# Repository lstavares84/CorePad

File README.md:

# CorePad — Beta Carbon

Macropad USB-C com **9 teclas em 3 × 3**, biometria, controle de áudio e gravação de reuniões. A linha escolhida para desenvolvimento é a **Beta**, com acabamento em aparência de fibra de carbono e faixa RGB configurável exclusivamente na base.

O [Caderno de Engenharia Rev. A em PDF](docs/engineering/Rev_A/CorePad_Caderno_de_Engenharia_Rev_A.pdf) consolida requisitos, eletrônica, mecânica, firmware, software, qualidade, riscos e pendências em 65 lâminas A3. Consulte o [índice e instruções de reprodução](docs/engineering/Rev_A/README.md). O caderno é uma linha de base de engenharia; fabricação permanece bloqueada pelos itens “A DEFINIR”.

## RGB — cinco cores

Galeria da [Beta 1.0.1](beta_blender/Beta_v1.0.1.blend), renderizada em 2000 × 1700 pixels com a mesma câmera e iluminação. A revisão refina a trama twill 2 × 2 de carbono, filamentos, resina, microtexturas e reflexos, e acrescenta um anteparo interno à faixa RGB.

| Laranja | Amarelo |
|---|---|
|  |  |
| Cor de referência sRGB `#FF6A00`. | Cor de referência sRGB `#FFD500`. |

| Verde | Vermelho |
|---|---|
|  |  |
| Cor de referência sRGB `#00FF00`. | Cor de referência sRGB `#FF1200`. |

**Azul — referência sRGB `#0066FF`**

## Produto: vistas técnicas

As vistas de topo, lateral e traseira preservam a documentação geométrica da [Beta 1.0.0](beta_blender/Beta_v1.0.0.blend); o detalhe dos controles usa os materiais refinados da [Beta 1.0.1](beta_blender/Beta_v1.0.1.blend). Elas mostram a organização visual escolhida; o empilhamento interno ainda está em desenvolvimento.

| Vista superior | Controles e biometria |
|---|---|
|  |  |
| Nove teclas sem inscrições, seletor, três indicadores e botão de gravação. | Fader vertical e mudo à direita, com sensor biométrico acessível. |

| Lateral esquerda | Traseira |
|---|---|
|  |  |
| P2 e microSD na lateral esquerda. | USB-C exclusivamente na borda traseira. |

**Detalhe da base — Beta 1.0.1**

Luz difusa junto à mesa, com anteparo interno e sem linha verde superior.

## PCB: estado atual dos arquivos KiCad

**Revisão ativa 0.3.0 — placas e encaixe:** a [PCB UI de duas camadas](development/hardware/v0.3.0/CorePad_UI_v0.3.0.kicad_pcb) contém nove footprints piloto Kailh Choc V2, FFC de 24 vias e **seis de nove sinais de teclas roteados**. A [PCB principal de quatro camadas](development/hardware/v0.3.0/CorePad_Main_v0.3.0.kicad_pcb) posiciona MCU, codec, amplificador, USB-C, microSD, P2 e FFC com footprints candidatos; não possui circuito completo nem trilhas funcionais. Consulte o [guia eletrônico](development/hardware/v0.3.0/README.md), a [pinagem proposta](development/hardware/v0.3.0/interconnect_24.json), a [BOM atualizada dos componentes posicionados](development/hardware/v0.3.0/BOM_DELTA.md) e os relatórios DRC: [UI](development/hardware/v0.3.0/ui_drc.txt) e [principal](development/hardware/v0.3.0/main_drc.txt).

| Trilhas piloto da UI | Componentes candidatos na principal |
|---|---|
|  |  |
| Três sinais de tecla e terra ainda abertos; DRC sem violações geométricas. | Posicionamento apenas; DRC com 8 violações, sem esquema completo. |

O [conjunto STEP integrado 0.2.0](development/integration/v0.2.0/CorePad_Beta_PCB_match_v0.2.0.step) substitui as placas nuas anteriores pelas exportações KiCad 0.3.0 e adiciona envelopes dos componentes e FFC. O [relatório de encaixe](development/integration/v0.2.0/README.md) identifica **choques do USB-C e microSD com a base**, desvio vertical **2,41 mm** entre P2 e abertura, ausência de suportes das placas e dobra do FFC ainda não comprovada. Esses achados impedem liberação para fabricação.

### Estudos anteriores

Os renders abaixo mostram o estudo 0.2.0 de bancada e posicionamento anterior. Não representam as placas ativas 0.3.0.

| Interface de bancada | Placa principal em estudo |
|---|---|
|  |  |
| 15 footprints de conectores, 44 pinos conferidos com o esquema e redes atribuídas. ERC sem erros/avisos; 29 conexões ainda sem trilhas. | Contorno e footprint do STM32U5A5. Áudio, alimentação, segurança, esquema completo e roteamento ainda pendentes. |

A interface usa chicotes para os controles externos e serve à bancada; a placa superior definitiva ainda precisa ser projetada. **As placas atuais não estão liberadas para fabricação.**

O [arquivo KiCad de posicionamento da PCB UI](development/hardware/ui_mechanical/v0.1.0/CorePad_UI_Posicionamento_v0.1.0.kicad_pcb) registra contorno e centros de teclas/controles na mesma referência do 3D; não tem pads, trilhas ou esquema.

**PCB UI mecânica:** nove centros SW1–SW9 e posições de controles; os retângulos mostram janelas da tampa, não footprints de solda.

- [Interface: esquema](development/hardware/v0.2.0/CorePad_Interface_Bancada_v0.2.0.kicad_sch) e [PCB](development/hardware/v0.2.0/CorePad_Interface_Bancada_v0.2.0.kicad_pcb).
- [Principal: PCB em estudo](development/hardware/v0.2.0/CorePad_Principal_v0.2.0.kicad_pcb).
- [BOM por bloco](development/hardware/v0.2.0/BOM.md), [arquitetura de referência](development/hardware/v0.2.0/ARCHITECTURE_REFERENCE.md) e [relatórios ERC/DRC](development/hardware/v0.2.0/reports/).

## Peças plásticas: vistas de engenharia

Renders derivados da [montagem mecânica editável](development/mechanical/v0.1.0/Beta_Pecas_v0.1.0.blend), revisão 0.1.0. As peças são mostradas sem revestimento decorativo para facilitar a leitura dos recortes e volumes.

**Vista explodida:** base isolante, difusor perimetral destacado em verde, tampa com recortes e dois botões. As separações verticais servem à visualização da montagem.

| Interior da base | Tampa vista de cima |
|---|---|
|  |  |
| Canal do difusor, pontes estruturais e aberturas de conectores/microfones. | Recortes das nove teclas, biometria, fader, chave, seletor, LEDs e gravação. |

O estudo mecânico usa **104 × 84 × 28,4 mm**, excluindo comandos. A espessura é exploratória e difere do modelo visual Beta. Cada STL contém um sólido fechado; fixações, suportes de PCB, retenções e tolerâncias dos componentes ainda precisam ser fechados.

## Montagem 3D integrada e desenhos — estudo anterior 0.1.0

O [conjunto STEP 0.1.0](development/integration/v0.1.0/CorePad_Beta_integrado_v0.1.0.step) documenta a geometria original da base, tampa, difusor, bateria e cabos. Usa a [PCB UI mecânica anterior](development/hardware/ui_mechanical/v0.1.0/CorePad_UI_Posicionamento_v0.1.0.kicad_pcb), sem pads/trilhas. A [fonte paramétrica](development/integration/v0.1.0/build_assembly.py), [peças STEP/STL](development/integration/v0.1.0/parts/), [manifesto](development/integration/v0.1.0/assembly_manifest.json) e [relatório anterior](development/integration/v0.1.0/fit_report.json) permanecem como histórico de engenharia. Para conferir a eletrônica atual com a caixa, use a **revisão 0.2.0** ligada acima.

**Conjunto montado:** caixa, placas, bateria, controles e cabos na posição nominal. A vista não prova encaixe de componentes de fornecedor.

As vistas de engenharia usam cinza neutro para leitura das peças; o acabamento escolhido continua sendo o carbono da galeria Beta 1.0.1 acima.

| Montagem explodida | Corpo aberto em posição montada |
|---|---|
|  |  |
| Vista para ler o empilhamento de tampa, PCB UI, PCB principal, bateria e base. | Base transparente de inspeção; conectores e cabos estão em posição proposta. |

**Passagem proposta:** a vista isola o FFC de 16 sinais e os dois fios da bateria; PCB UI, tampa e comandos foram ocultados apenas para inspeção. Conectores, terminação, comprimento e raio de dobra ainda não foram escolhidos.

| Planta cotada preliminar | Seção do empilhamento preliminar |
|---|---|
|  |  |
| Envelope 104 × 84 mm e localização de controles. | Alturas das placas, bateria, tampa e folgas nominais. |

Consulte a [BOM mecânica e de cabos](development/integration/v0.1.0/BOM_MECANICA_CABOS.md) e o [índice de liberação de manufatura](development/integration/v0.1.0/LIBERACAO_MANUFATURA.md). Os desenhos são estudo dimensional; **não são desenhos liberados para fabricar**.

[Base STL](development/mechanical/v0.1.0/Base_plastica.stl) · [Tampa STL](development/mechanical/v0.1.0/Tampa_carbono.stl) · [Difusor STL](development/mechanical/v0.1.0/Difusor_RGB.stl) · [Botão de camada STL](development/mechanical/v0.1.0/Botao_camada.stl) · [Botão de gravação STL](development/mechanical/v0.1.0/Botao_gravacao.stl)

## Software e verificação

O [firmware C11](development/firmware/) contém o núcleo de estados de camadas, cartão, RGB e bateria baixa, testado em host e compilado para Cortex-M33. O [configurador desktop](development/software/configurator.py) edita as 18 macros comuns e RGB, salva JSON e aplica a configuração a um simulador. USB físico, drivers de áudio/cartão, biometria segura e FIDO2 continuam em desenvolvimento.

O [enquadramento de configuração pública](development/software/wire_protocol.py) já valida versão, tamanho, ID de mensagem e CRC32 antes de entregar comandos ao simulador. Ainda não é comunicação USB de produto.

```sh
make -C development/firmware test arm
python3 -m unittest discover -s development/tests -v
python3 development/software/configurator.py
```

Consulte [resultados de validação](development/VALIDATION.md), [estado atual](docs/STATUS.md) e [roteiro](docs/ROADMAP.md). A autonomia de 30 horas permanece como meta de ensaio.

## Continuar o desenvolvimento

Comece por [CLAUDE.md](CLAUDE.md), pela [especificação vigente](Especificacao_Produto_Macropad_Biometrico_Gravador_2026-11-21.md) e pelo [guia integrado](development/README.md).

| Caminho | Conteúdo ativo |
|---|---|
| `beta_blender/` | Design Beta carbon, gerador e vistas do produto |
| `development/hardware/` | KiCad, BOM, arquitetura e relatórios |
| `development/firmware/` | Núcleo C e testes |
| `development/software/` | Configurador, protocolo e referência RF64 |
| `development/mechanical/` | Montagem Blender, STL e gerador das peças |
| `development/integration/` | Conjunto CAD integrado, desenhos, encaixe e BOM mecânica/chicotes |
| `docs/` | Estado, roteiro, renders técnicos e scripts de renderização |
| `.old/` | Alpha, conceitos substituídos e duplicatas; somente histórico |

As fontes dos renders e os comandos para reproduzi-los estão em [docs/render/README.md](docs/render/README.md). Revisões entregues devem ser preservadas, com novas versões em `MAJOR.MINOR.PATCH`.

Projeto privado em desenvolvimento. Nenhuma licença de distribuição foi concedida.

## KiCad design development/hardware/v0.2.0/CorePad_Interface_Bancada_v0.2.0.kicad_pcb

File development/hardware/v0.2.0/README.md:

# Eletrônica CorePad Beta 0.2.0

## Arquivos e limites

`CorePad_Interface_Bancada_v0.2.0.kicad_sch` contém esquema elétrico de conectores para testar nove teclas e controles externos. `CorePad_Interface_Bancada_v0.2.0.kicad_pcb` contém footprints e redes correspondentes. Os conectores J1–J9 recebem fios dos switches reais; **não são footprints dos Kailh Choc V2**. O PCB não foi roteado. Esta interface é um apoio de bancada e não substitui a placa superior do produto.

`CorePad_Principal_v0.2.0.kicad_pcb` contém contorno e footprint do STM32U5A5. O esquema pino a pino, passivos e redes da principal ainda precisam ser desenvolvidos. O estudo Alpha 0.1.0 permanece como origem da arquitetura, com os riscos registrados.

A [PCB UI de posicionamento mecânico](../ui_mechanical/v0.1.0/README.md) agora compartilha com o conjunto 3D o contorno e os centros dos controles. Ela **não** substitui esta interface elétrica de bancada, nem é ainda uma PCB de produto: não tem pads, footprints reais ou roteamento.

Todos os sinais da interface são referidos a GND e trabalham no domínio 3,3 V. Teclas usam pull-up no controlador e fecham contra GND. `MUTE_SENSE` é somente leitura da posição: o corte físico dos microfones permanece na placa principal. `FADER` recebe o cursor de um potenciômetro de 10 kohm entre 3V3 e GND, sujeito a filtro/proteção na principal. J14 alimenta a referência de bancada; conferir o manifesto antes de ligar.

## Recursos a reservar na principal

| Bloco | Interface necessária | Fechamento pendente |
|---|---|---|
| USB | OTG HS, D+/D−, VBUS sense, proteção | USB composto e orçamento de endpoints; CC integrado versus controlador externo |
| Cartão | SDMMC CLK/CMD/D0–D3 + detecção | Pinos/AF, resistores série, pull-ups e ESD |
| Codec | SAI RX/TX/BCLK/FS/MCLK + I2C | Relógio simultâneo, DMA, alimentação e filtragem |
| Segurança | I2C autenticado + enable | Provisionamento, TrustZone e política de depuração |
| Biometria | A definir com sensor seguro | Não aceitar resultado UART como autenticação de produção |
| Teclas | 9 GPIO | Sem matriz elétrica; 3 × 3 é disposição física |
| Auxiliares | 3 GPIO + ADC + detecção SD | Fader, camada, gravação e leitura de mudo |
| LEDs | 3 GPIO + indicador REC | Correntes e ótica |
| RGB | PWM/driver a selecionar + chave de carga | Ripple/ruído acústico, consumo e brilho |
| Alimentação | I2C, alertas, NTC, SWD/RESET | Corrente USB, célula, carga e partida com bateria esgotada |

Não atribuir números de pinos antes de conferir todas as funções alternativas na ficha da variante exata. As interfaces acima não constituem validação de coexistência.

## Fontes consultadas em 22/11/2026

- ST: https://www.st.com/en/microcontrollers-microprocessors/stm32u5a5zj.html
- ST, ficha da família/variante: https://www.st.com/resource/en/datasheet/stm32u5a5zj.pdf
- TI, codec: https://www.ti.com/product/TAC5112
- Kailh, switches: https://www.kailh.net/products/kailh-choc-v2-low-profile-switch-set
- Demais candidatos: fontes primárias no relatório Alpha 0.1.0, ainda exigindo reconferência por componente antes do esquema.

DRC e netlist ficam em `reports/`. Violações de conexão aberta são esperadas nesta revisão não roteada. Não gerar compra integral ou fabricação a partir dela.

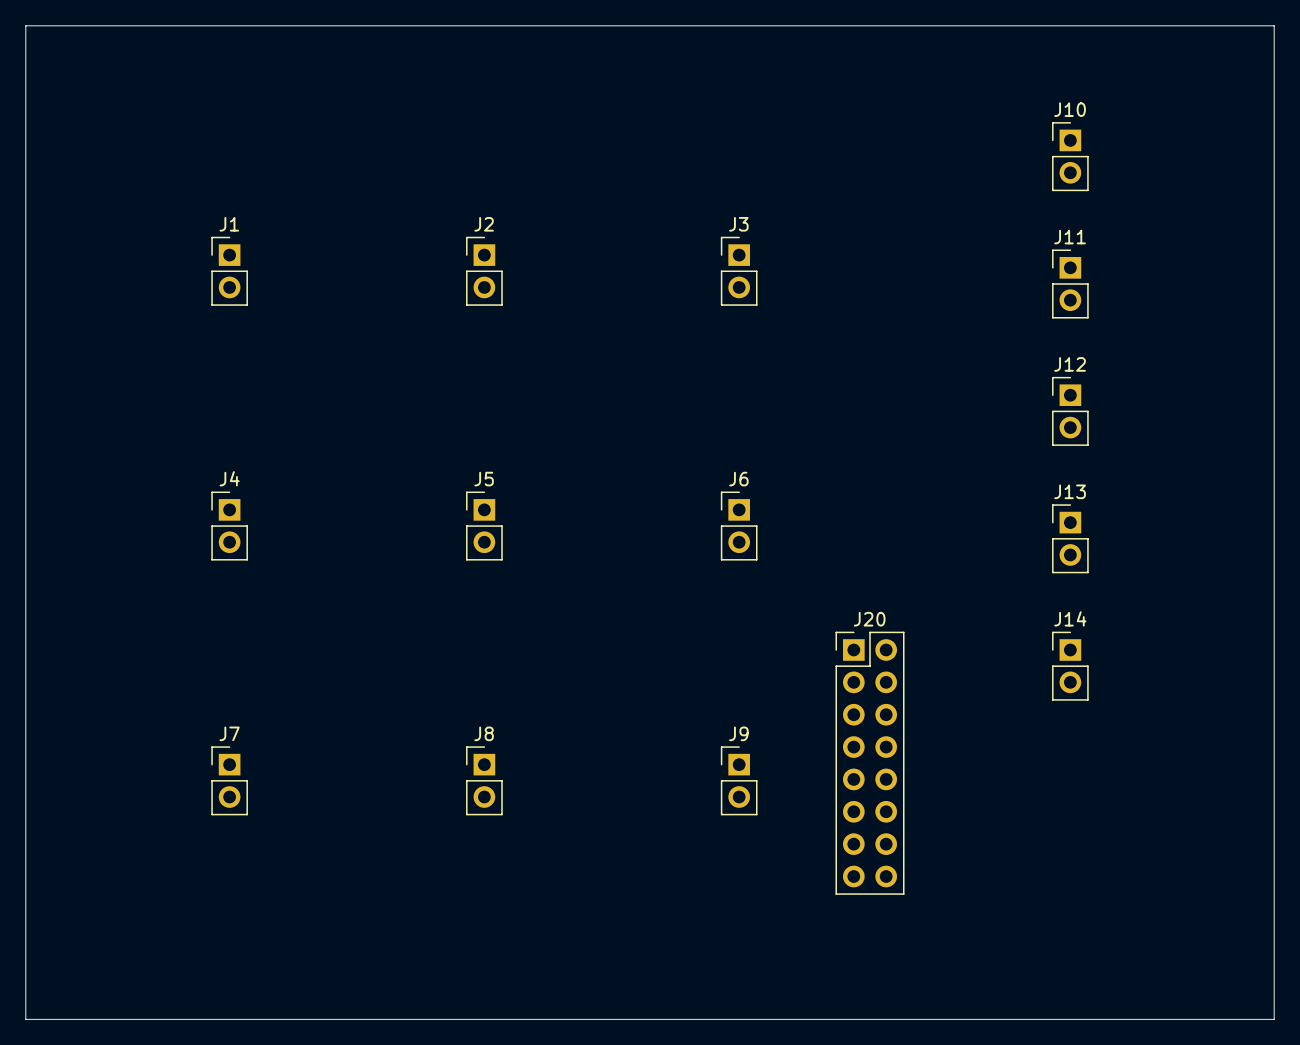
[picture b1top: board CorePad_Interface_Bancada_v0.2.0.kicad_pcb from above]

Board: 2 copper layers, 98.0 x 78.0 mm, 15 parts (0 on the bottom side), 15 nets, no tracks yet.

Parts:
J1: External key 1; PinHeader_1x02_P2.54mm_Vertical
J2: External key 2; PinHeader_1x02_P2.54mm_Vertical
J3: External key 3; PinHeader_1x02_P2.54mm_Vertical
J4: External key 4; PinHeader_1x02_P2.54mm_Vertical
J5: External key 5; PinHeader_1x02_P2.54mm_Vertical
J6: External key 6; PinHeader_1x02_P2.54mm_Vertical
J7: External key 7; PinHeader_1x02_P2.54mm_Vertical
J8: External key 8; PinHeader_1x02_P2.54mm_Vertical
J9: External key 9; PinHeader_1x02_P2.54mm_Vertical
J10: LAYER; PinHeader_1x02_P2.54mm_Vertical
J11: RECORD; PinHeader_1x02_P2.54mm_Vertical
J12: MUTE_SENSE; PinHeader_1x02_P2.54mm_Vertical
J13: FADER; PinHeader_1x02_P2.54mm_Vertical
J14: 3V3; PinHeader_1x02_P2.54mm_Vertical
J20: Interface 3V3; PinHeader_2x08_P2.54mm_Vertical

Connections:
3V3: J14.1, J20.14
FADER: J13.1, J20.13
GND: J1.2, J2.2, J3.2, J4.2, J5.2, J6.2, J7.2, J8.2, J9.2, J10.2, J11.2, J12.2, J13.2, J14.2, J20.15, J20.16
KEY1: J1.1, J20.1
KEY2: J2.1, J20.2
KEY3: J3.1, J20.3
KEY4: J4.1, J20.4
KEY5: J5.1, J20.5
KEY6: J6.1, J20.6
KEY7: J7.1, J20.7
KEY8: J8.1, J20.8
KEY9: J9.1, J20.9
LAYER: J10.1, J20.10
MUTE_SENSE: J12.1, J20.12
RECORD: J11.1, J20.11

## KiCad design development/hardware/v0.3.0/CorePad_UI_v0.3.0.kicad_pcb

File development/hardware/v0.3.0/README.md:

# CorePad Beta Carbon — eletrônica 0.3.0

Revisão de **posicionamento eletromecânico e roteamento piloto**, não um pacote de fabricação. A placa principal tem footprints de componentes candidatos e redes de portas; ainda não tem esquema elétrico completo, ligação pino a pino do MCU, alimentação, proteção, vias de terra ou trilhas funcionais. A placa de interface tem nove footprints piloto de switch, FFC de 24 vias e seis sinais de tecla roteados. Os DRCs são preservados sem exclusões.

## Arquivos

| Arquivo | Conteúdo |
|---|---|
| `CorePad_UI_v0.3.0.kicad_pcb` | Placa de 98 × 78 mm, duas camadas; SW1–9 e J_UI; KEY1, 2, 3, 5, 6 e 9 roteadas |
| `CorePad_Main_v0.3.0.kicad_pcb` | Placa de 98 × 78 mm, quatro camadas; MCU, codec, amplificador, USB-C, microSD, P2, FFC |
| `interconnect_24.json` | Alocação elétrica proposta de pinos do cabo flexível |
| `BOM_DELTA.md` | Componentes colocados ou alterados frente à BOM funcional 0.2.0 |
| `switch_placement.json` | Centros, envelope e terminais dos nove switches |
| `CorePad.pretty/` | Footprint **piloto** Choc V2 baseado em desenho do fabricante; espelhamento e pinos a conferir com amostra |
| `ui_drc.txt`, `main_drc.txt` | Relatórios completos de 22/11/2026 |
| `build_pcbs.py`, `route_ui.py` | Fontes para regenerar as placas e trilhas piloto |

Vermelho: F.Cu; azul: B.Cu. Há seis rotas completas e três abertas. As trilhas estreitas de `0,15 mm`, clearance de `0,20 mm` e vias `0,60/0,30 mm` são **parâmetros do estudo**, não requisitos liberados ao fabricante. O roteador usa malha de `0,25 mm`, não otimiza comprimento nem retorno de corrente. Revisar seus longos desvios no editor PCB antes de adicionar plano de terra.

A placa principal mostra **posicionamento**; o retângulo do MCU ainda não demonstra que todos os periféricos cabem em sua pinagem simultânea. Os volumes reservados para carga, elemento seguro, microfones e RGB estão em `Dwgs.User` e não são footprints montáveis.

## Pinos entre as placas

Conector candidato Amphenol `F32R-1A7H1-11024`, 24 vias, passo `0,5 mm`, altura nominal `2 mm`. Ambos ficam no datum XY `(-30; +33,5) mm`; o da UI está na face inferior. Pinos e funções são **reserva**, não rede elétrica comprovada. Corrente de alimentação, orientação de contato do FFC, comprimento e raio de dobra continuam abertos.

| Pinos | Função proposta | Estado |
|---|---|---|
| 1–9 | Uma entrada independente por tecla | 1,2,3,5,6,9 roteadas na UI; 4,7,8 abertas |
| 10–11 | Seletor de camada e gravação | Componentes por escolher |
| 12–13 | Leitura de mudo e ADC do fader | Componentes e circuito por escolher |
| 14–16 | 3V3_UI e dois retornos GND | Corrente, ruído e aterramento por dimensionar |
| 17 | `MUTE_HW_EN` direto ao circuito de mudo na principal | Sem implementação; independência do firmware a provar |
| 18–20 | UART TX/RX e reset do sensor biométrico | Sensor seguro por selecionar |
| 21–24 | Três indicadores de camada e indicador de gravação | LEDs, resistores e guias ópticos por selecionar |

RGB da base fica na placa principal ou em chicote próprio, não consome pinos deste FFC. A arquitetura acima depende de a biometria final aceitar esses três sinais e da alimentação `3V3_UI`; outra seleção pode exigir novo conector. A chave física de mudo deve acionar eletrônica de isolamento dos microfones **sem depender de comando do MCU**; `MUTE_SENSE` serve só para interface. Não interligar cápsulas analógicas diretamente pelo FFC antes de definir o circuito.

## Componentes candidatos posicionados

| Ref. | Fabricante / MPN | Encapsulamento e condição |
|---|---|---|
| SW1–9 | Kailh CPG135301D01 Choc V2 Red | 15 × 15 mm; corpo 6,4 mm acima da PCB; footprint piloto requer amostra |
| J_UI nas duas placas | Amphenol F32R-1A7H1-11024 | Footprint KiCad de 24 vias; cabo ainda sem código |
| U1 | ST STM32U5A5ZJT6Q | LQFP-144 20 × 20 mm; pinos sem atribuição |
| U2 | TI TAC5112IRGER | VQFN-24 4 × 4 mm genérico; pad térmico a validar no land pattern TI |
| U3 | TI TPA6132A2RTER | WQFN-16 3 × 3 mm; land pattern a comparar com TI |
| J_USB | GCT USB4105-GF-A | Footprint KiCad da família; quatro violações de isolamento furo/pad |
| J_SD | Hirose DM3AT-SF-PEJM5 | 15,95 × 13,85 × 1,68 mm; duas violações de serigrafia/borda e choque mecânico |
| J_P2 | Same Sky SJ-3523-SMT-TR | Altura de corpo 5 mm, centro do plug 2,5 mm acima da PCB; duas violações de serigrafia/borda |

`U7 BQ25622` é **WQFN-HR de 18 pinos**, e não deve receber footprint pelo número de pinos presumido da BOM anterior. A chave DPDT de alavanca `7201SYZQE` é alta e de terminais soldáveis; sua escolha mecânica foi suspensa. Candidatos compactos só entram após comprovar operação, contatos, abertura da tampa e circuito de mudo.

## Regras para fechar o roteamento

1. Selecionar os componentes faltantes e completar **esquema + pinmap**: USB, SDMMC, I²S/TDM, I²C, ADC, UART, FFC, mudo físico, energia, LEDs e biometria.
2. Confirmar stack-up FR4 de quatro camadas e impedância USB com o fabricante. Usar plano de retorno contínuo sob USB e áudio; largura/espaçamento do diferencial ainda não foi calculada.
3. Posicionar microfones com dutos da caixa, afastando entradas de áudio de reguladores e cartão. Definir retorno de cápsulas, desacoplamento junto aos pinos, proteção ESD e trilhas de bateria/carga pelo consumo medido.
4. Resolver os choques mecânicos e instalar furos/suportes de ambas as placas antes de congelar portas e FFC. Atualizar esquemas e PCB juntas; não ocultar itens do DRC.
5. Só então rotear, gerar Gerber, furação, pick-and-place e BOM de compra. Validar DRC/ERC e protótipo físico.

**Estado do DRC:** UI 0 violações geométricas e 13 conexões abertas; principal 8 violações (4 USB furo/pad, 4 serigrafia nas bordas) e 8 conexões abertas apenas entre pads já nomeados. Mais conexões aparecerão quando o esquema completo for inserido. Os 6 sinais de tecla roteados não indicam funcionamento do dispositivo.

## Fontes de dimensões

- [Kailh, Choc V2 Red](https://cdn.shopify.com/s/files/1/0657/6075/5954/files/SPEC-CPG135301D01_Kailh_Choc_V2_Low_Profile_Red_Switch.pdf?v=1666690444)
- [Amphenol, F32R 24 vias](https://www.amphenol-cs.com/product/f32r1a7h111024.html)
- [Hirose, DM3AT-SF-PEJM5](https://www.hirose.com/en/product/p/CL0609-0031-0-00)
- [Same Sky, SJ-3523-SMT-TR](https://www.sameskydevices.com/product/resource/sj-352x-smt.pdf)
- [ST, STM32U5A5ZJ](https://www.st.com/en/microcontrollers-microprocessors/stm32u5a5zj.html)
- [TI, TPA6132A2](https://www.ti.com/product/TPA6132A2/part-details/TPA6132A2RTER)
- [TI, BQ25622](https://www.ti.com/product/BQ25622)
- [Bourns, PTA1543](https://www.bourns.com/data/global/pdfs/PTA.pdf)

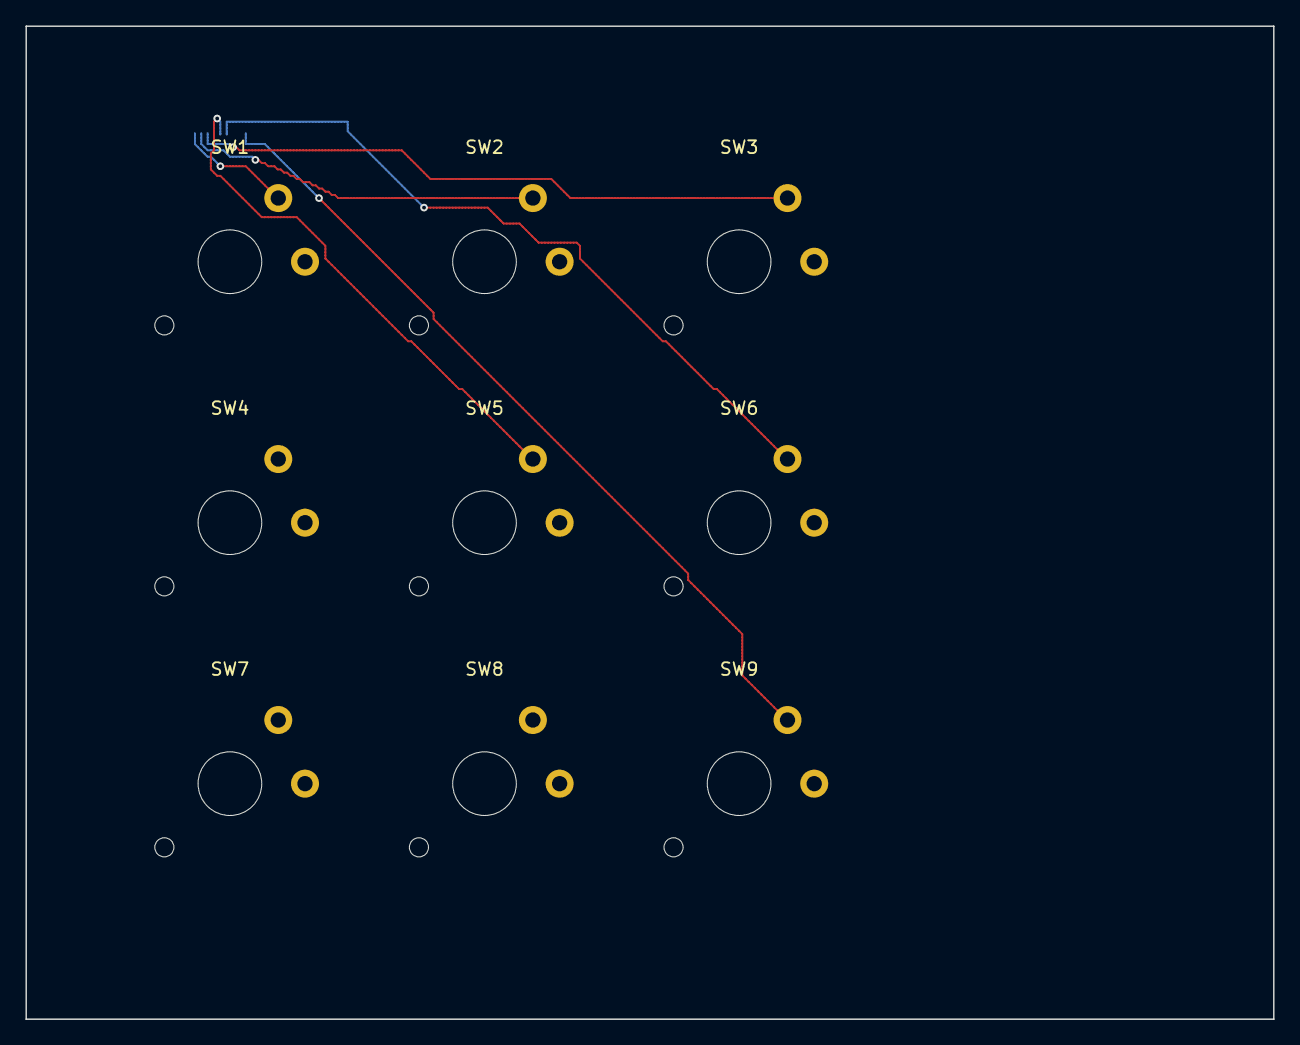
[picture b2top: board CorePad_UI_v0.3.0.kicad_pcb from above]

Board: 2 copper layers, 98.0 x 78.0 mm, 10 parts (1 on the bottom side), 10 nets.

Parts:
J_UI: F32R-1A7H1-11024 CANDIDATE; Amphenol_F32R-1A7x1-11024_1x24-1MP_P0.5mm_Horizontal
SW1, SW2, SW3, SW4, SW5, SW6, SW7, SW8, SW9: CPG135301D01 PILOT; SW_Kailh_Choc_V2_CPG135301D01_Pilot

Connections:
GND: J_UI.15, J_UI.16, SW1.2, SW2.2, SW3.2, SW4.2, SW5.2, SW6.2, SW7.2, SW8.2, SW9.2
KEY1: J_UI.1, SW1.1
KEY2: J_UI.2, SW2.1
KEY3: J_UI.3, SW3.1
KEY4: J_UI.4, SW4.1
KEY5: J_UI.5, SW5.1
KEY6: J_UI.6, SW6.1
KEY7: J_UI.7, SW7.1
KEY8: J_UI.8, SW8.1
KEY9: J_UI.9, SW9.1

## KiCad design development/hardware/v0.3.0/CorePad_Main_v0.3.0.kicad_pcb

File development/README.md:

# CorePad Beta — desenvolvimento integrado 0.2.0

22/11/2026. A Beta em estilo fibra de carbono foi escolhida para seguir o desenvolvimento.

Esta entrega implementa a base de software e modelos de prototipagem. A placa principal permanece em engenharia: não existe ainda um produto completo que possa ser comprado, fabricado e usado com todas as funções.

| Entrega | Arquivo | Situação |
|---|---|---|
| Firmware portátil C11 | `firmware/corepad.c` | Estados de cartão, bloqueio de camada, RGB; testado em host e compilado para Cortex-M33 |
| Configurador desktop | `software/configurator.py` | Editor de 18 macros comuns e RGB; exportação JSON e simulador local |
| Protocolo | `software/device.py` | Contrato e validação de configuração; transporte USB físico pendente |
| Gravação RF64 | `software/rf64.py` | Escritor PCM de referência, testado com arquivo pequeno; não executa no MCU |
| Eletrônica KiCad | `hardware/v0.2.0/` | Esquema de bancada da interface e PCB com redes; principal com footprint MCU, sem esquema completo/roteamento |
| Placas ativas KiCad | `hardware/v0.3.0/` | UI com nove switches e FFC 24 vias, seis teclas roteadas; principal com footprints candidatos de MCU, áudio e portas |
| Peças plásticas | `mechanical/v0.1.0/` | Base, tampa, difusor e botões editáveis; STL para estudo de encaixe |
| BOM | `hardware/v0.2.0/BOM.md` | Lista por bloco com códigos candidatos e pendências; sem preço total fictício |
| Montagem 3D integrada | `integration/v0.1.0/` | STEP conjunto e peças, placa principal KiCad, volumes de reserva, cabos propostos, dois desenhos SVG e relatório de encaixe |
| Revisão PCB/caixa | `integration/v0.2.0/` | STEP das duas PCBs 0.3.0 com caixa e envelopes; USB-C/microSD colidem, P2 desalinhado, suportes ausentes |
| PCB UI mecânica | `hardware/ui_mechanical/v0.1.0/` | Contorno KiCad e centros dos controles, sem pads ou trilhas |
| Enquadramento de mensagens | `software/wire_protocol.py` | Quadro com ID, limite de tamanho e CRC32 testado no simulador; ainda sem USB físico |

## Executar

Na raiz do repositório:

```sh
make -C development/firmware test arm
python3 -m unittest discover -s development/tests -v
python3 development/software/configurator.py
```

O configurador usa Python 3 e Tkinter. O simulador e os testes usam apenas a biblioteca padrão. O alvo ARM gera um objeto compilado; startup, linker, HAL, USB Audio/HID/MSC, FatFs, codec e CTAP ainda precisam ser integrados.

## Sequência de engenharia pendente

1. Fechar a tabela de funções alternativas/pinos do STM32U5A5ZJT6Q com SDMMC, SAI e USB simultâneos.
2. Ensaiar USB Audio + gravação contínua em microSD com kit de desenvolvimento; medir consumo e latência.
3. Selecionar o sensor biométrico seguro. O módulo serial 4750 continua limitado a ergonomia/bancada.
4. Fechar esquemas da principal, desacoplamentos, carga, áudio, proteção e pinagem das interligações.
5. Validar os footprints de catálogo, empilhamento, curso das teclas, conectores e bateria com peças/modelos reais.
6. Rotear, revisar ERC/DRC, montar protótipo e medir os requisitos de áudio e 30 horas.

O [dossiê de manufatura](integration/v0.1.0/LIBERACAO_MANUFATURA.md) identifica desenhos, BOM, modelos e testes ainda necessários. A [revisão integrada atual](integration/v0.2.0/README.md) mede os choques de portas e a falta de fixação. Ambos os conjuntos STEP são estudos dimensionais, sem liberação de ferramental.

Não foi realizado ensaio de hardware nesta entrega. O relatório KiCad registra conexões ainda abertas. Não há Gerbers liberados.

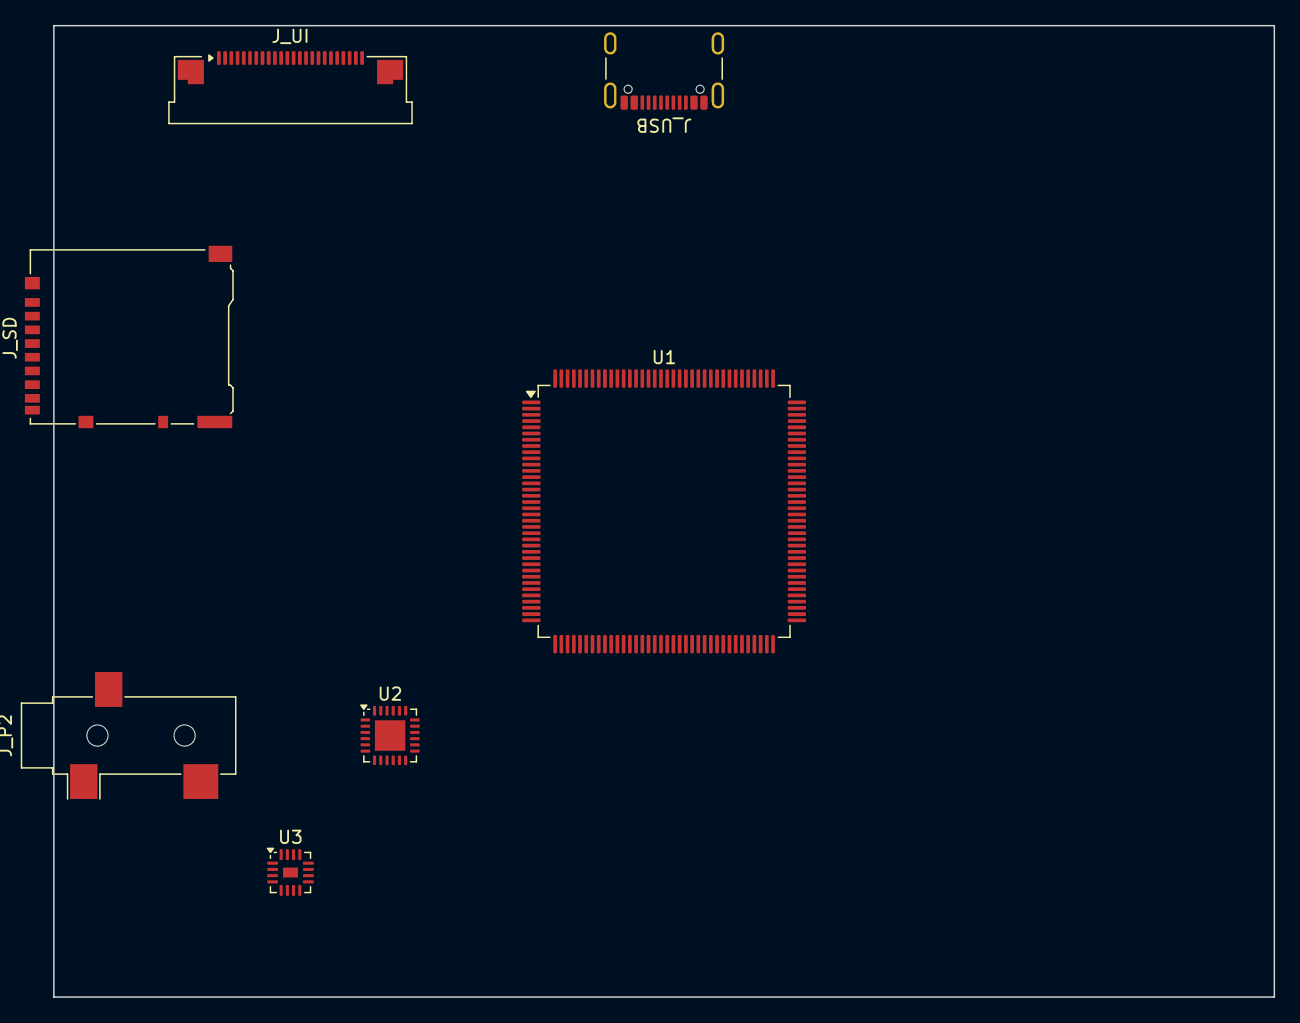
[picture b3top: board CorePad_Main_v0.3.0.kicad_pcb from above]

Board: 4 copper layers, 98.0 x 78.0 mm, 7 parts (0 on the bottom side), 4 nets, no tracks yet.

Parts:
J_P2: SJ-3523-SMT-TR CANDIDATE; Jack_3.5mm_CUI_SJ-3523-SMT_Horizontal
J_SD: DM3AT-SF-PEJM5 CANDIDATE; microSD_HC_Hirose_DM3AT-SF-PEJM5
J_UI: F32R-1A7H1-11024 CANDIDATE; Amphenol_F32R-1A7x1-11024_1x24-1MP_P0.5mm_Horizontal
J_USB: USB4105-GF-A CANDIDATE; USB_C_Receptacle_GCT_USB4105-xx-A_16P_TopMnt_Horizontal
U1: STM32U5A5ZJT6Q; LQFP-144_20x20mm_P0.5mm
U2: TAC5112IRGER LAND PATTERN TO CHECK; VQFN-24-1EP_4x4mm_P0.5mm_EP2.45x2.45mm
U3: TPA6132A2RTER LAND PATTERN TO CHECK; Texas_RTE_WQFN-16-1EP_3x3mm_P0.5mm_EP1.2x0.8mm

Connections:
GND: J_P2.S, J_SD.6, J_UI.15, J_UI.16, J_USB.A1, J_USB.A12, J_USB.B1, J_USB.B12
USB_D+: J_USB.A6, J_USB.B6
USB_D-: J_USB.A7, J_USB.B7
VBUS: J_USB.A4, J_USB.A9, J_USB.B4, J_USB.B9
